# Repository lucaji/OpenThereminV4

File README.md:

# OpenTheremin v4.x platformio IDE

a new fork for the open source Theremin instrument software and hardware project by [GaudiLabs](https://github.com/GaudiLabs/OpenThereminV4). Adapted for [platformio](https://platformio.org/) IDE. Schematics, printed circuit board (PCB) design, bill of materials (BOM) and Arduino UNO compatible software for the OpenTheremin v4.x

> This repository brings an refactored, cleaned, fully commented and slightly optimized firmware for all OpenTheremin v4.x boards.

Lots of experimentation with this firmware is possible, check `build.h` for options.

## Waveform interpolation

Three waveform interpolation algorithms are included for experimenting with the 328p DDS generation:

- NONE (LEGACY)
- LINEAR
- HERMITE
- CATMULL-ROM (pushing the limits of the 328p - computational hungry!)

There is an interactive mode where each mode can be selected by muting/unmuting the Theremin. Using the NONE (LEGACY) mode, gives anyway a clean spectrum content on the audio output, fast responsiveness and an extended pitch range because of the optimizations that were already in place in the original OpenTheremin firmware.

## Serial port configuration

- Off (saves resources!)
- DEBUG (gives some state information)
- MIDI (emits MIDI data at 31250bps)

## Open Source Theremin based on the Arduino Platform

OpenTheremin is an arduino based real Theremin instrument. The legendary music instrument was invented by [Leon Theremin](https://www.google.com/url?sa=t&source=web&rct=j&opi=89978449&url=https://it.wikipedia.org/wiki/Lev_Sergeevi%25C4%258D_Termen) back in 1920.

The Theremin is played with both hands around two antennas, one to control the pitch and the other for volume expressivity.

The fully assembled version 4.x of OpenTheremin leverages two heterodyne VCO oscillators (voltage controlled) to measure the distance of the hands to each antenna while playing the instrument, by comparing those frequencies with two fixed frequency local oscillators.

The resulting signals (beating) are fed to and processed by a AtMega328P microcontroller which applies linearization and filtering in real-time, generating the sound reflecting the player's hands movements in the thin air.

There is an fast audio DAC onboard which delivers high quality digital audio, generated via a DDS (Direct Digital Synthesis) synth accessing serveral user-presettable and customizable wavetables to achieve different timbres.

## Instructions

This repo favours [VSCode + Platformio IDE](https://platformio.org/install/ide?install=vscode) as development environment instead of the Arduino IDE, still retaining compatibility though.

To fully enjoy a better development experience, it is advised to install Visual Studio Code and add the platformio IDE plug-in. After the latter has been installed, just opening the folder in VS Code will activate the platformio IDE.

## Ordering preassembled and tested boards

For more info on the open source project and on availability of ready made shield see:

https://www.gaudi.ch/OpenTheremin/

## Limits

> please be aware that the included DDS sound generator algorithm on a 16MHz 328p (Arduino UNO compatible) which is hardware driven by a two etherodyne RF VCO (voltage controlled oscillators) is already pushing the limits of the internal timers and interrupt pressure.

The lesser additional options you include in the build, the better sound quality:

- keep the serial port disabled if you don't need it.
- disable the CV/GATE outputs if you don't need them.
- select the desired interpolation mode if you like one - OFF otherwise!

#### LAST REVISION:

July 2025 by Luca Cipressi (lucaji.github.io)

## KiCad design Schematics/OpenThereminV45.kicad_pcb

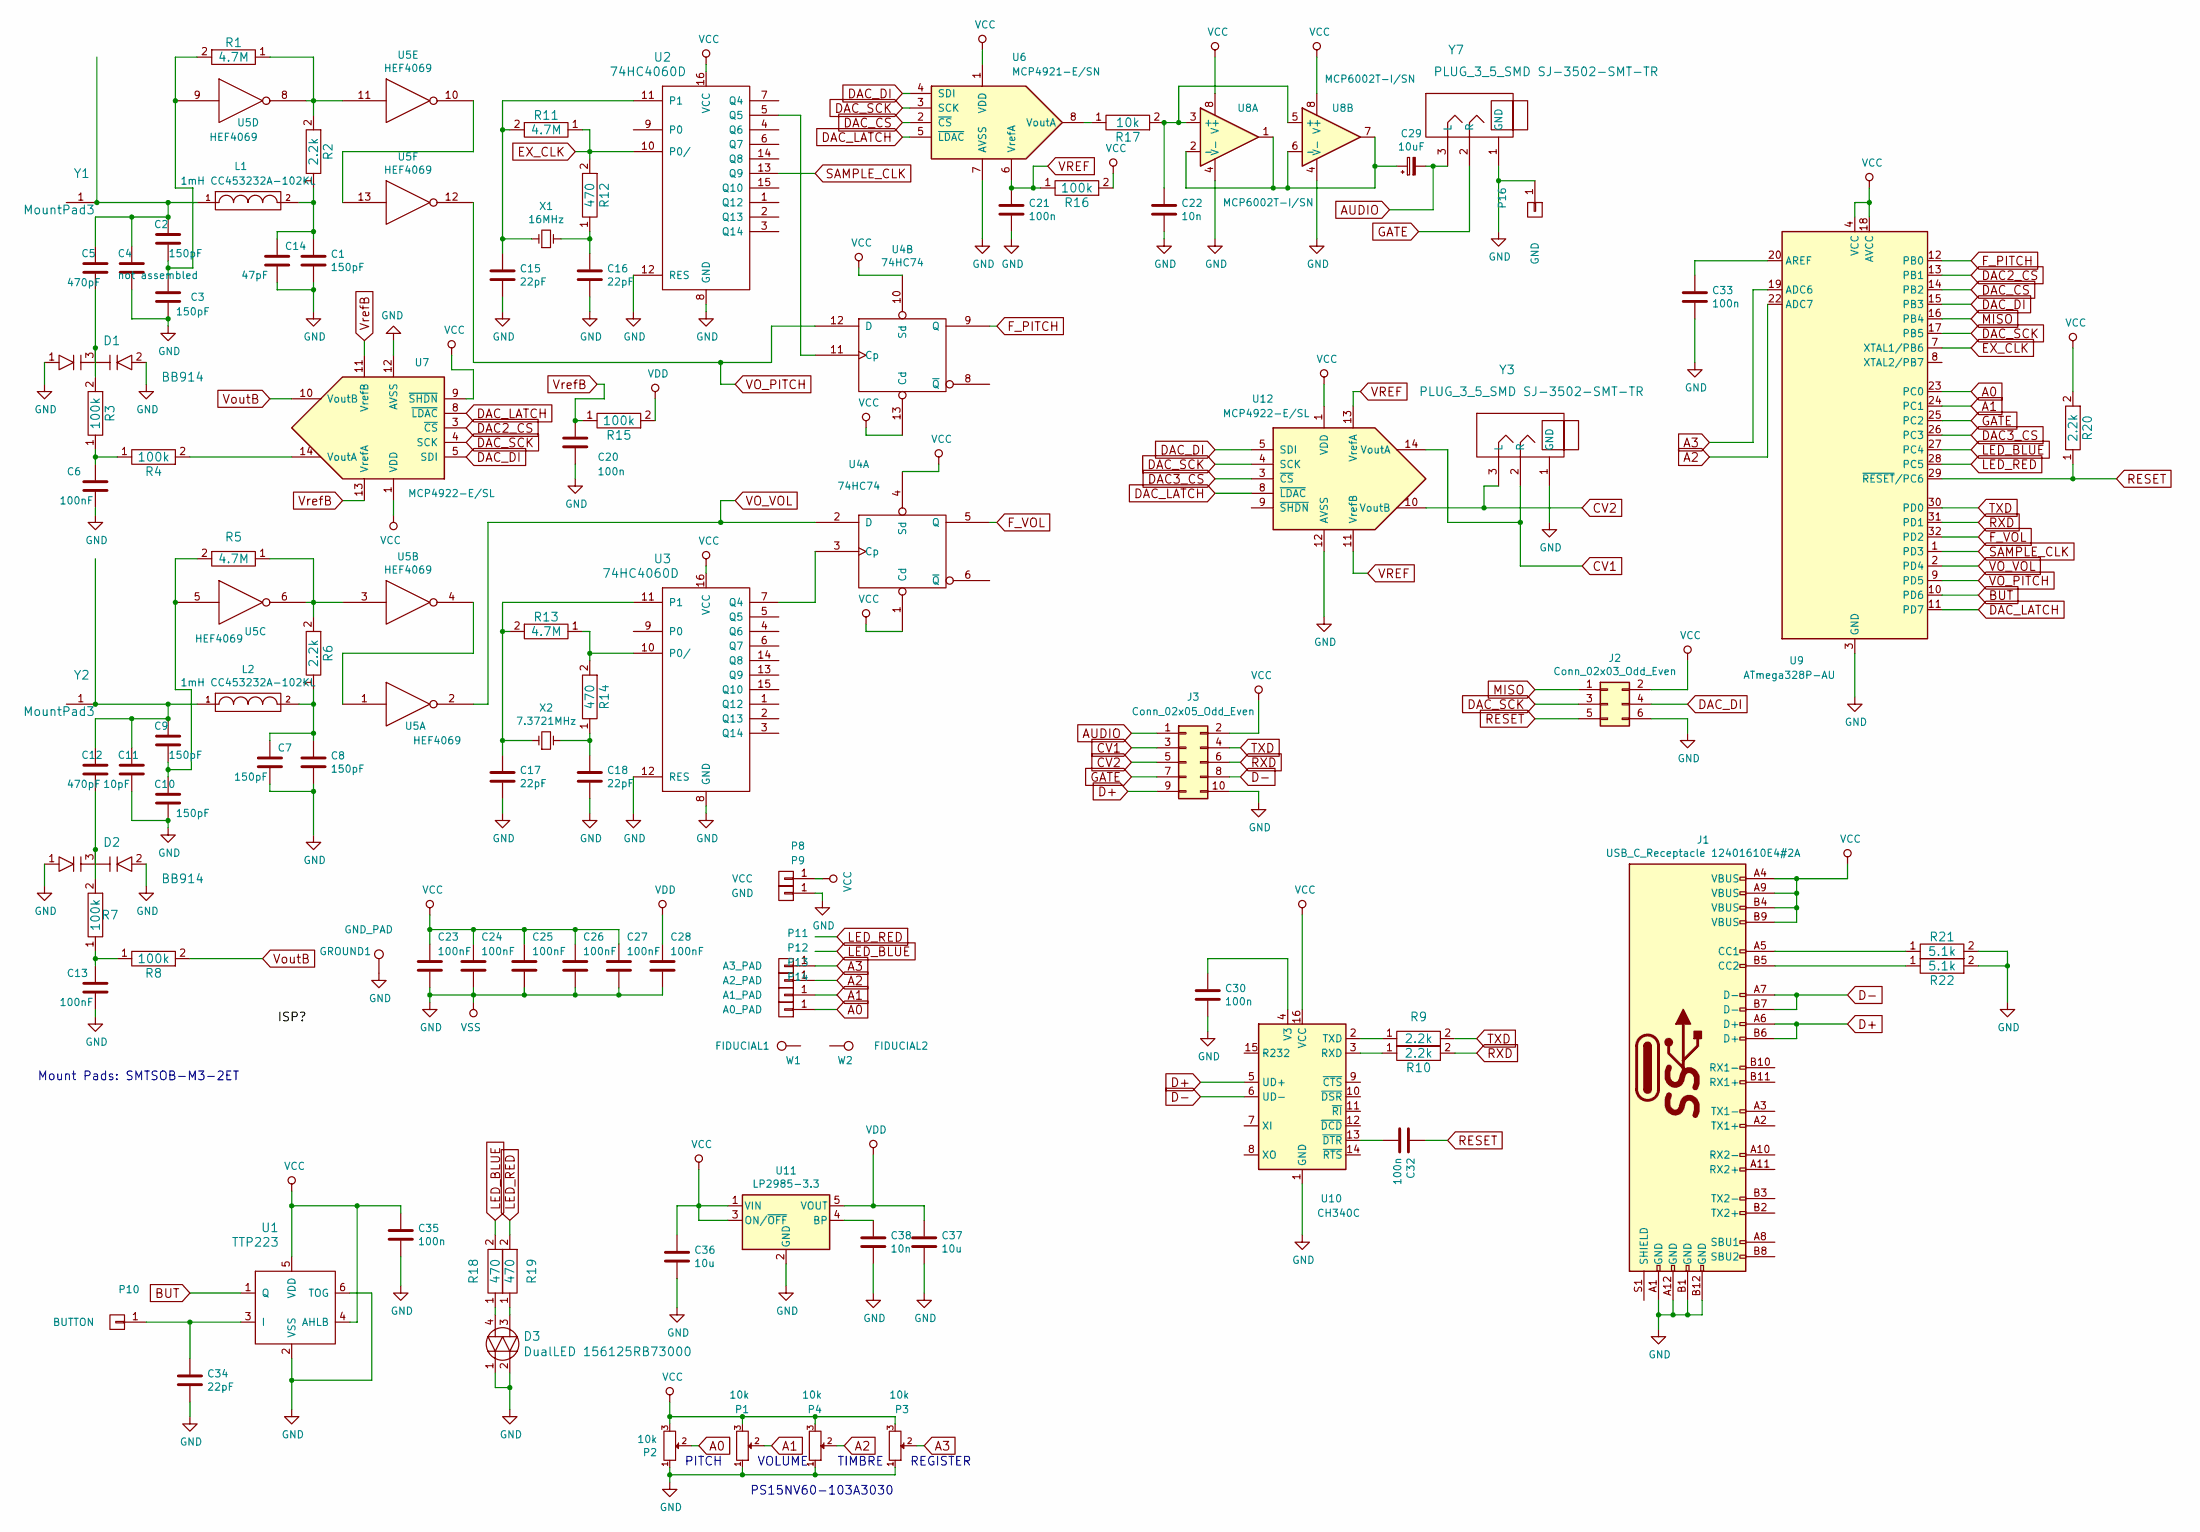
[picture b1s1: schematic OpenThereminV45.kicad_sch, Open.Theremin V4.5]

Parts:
C1, C2, C3, C7, C8, C9, C10: 150pF; C_0603_1608Metric
C4: not assembled; C_0603_1608Metric
C5, C12: 470pF; C_0603_1608Metric
C6, C13, C23, C24, C25, C26, C27, C28: 100nF; C_0603_1608Metric
C11: 10pF; C_0603_1608Metric
C14: 47pF; C_0603_1608Metric
C15, C16, C17, C18, C34: 22pF; C_0603_1608Metric
C20, C21, C30, C32, C33, C35: 100n; C_0603_1608Metric
C22, C38: 10n; C_0603_1608Metric
C29: 10uF; C_0603_1608Metric
C36, C37: 10u; C_0603_1608Metric
D1, D2: BB914; SOT-23
D3: DualLED 156125RB73000; WL-SBRW
GROUND1: GND_PAD; GNDPad
J1: USB_C_Receptacle 12401610E4#2A; USB_C_Receptacle_Amphenol_12401610E4-2A
J2: Conn_02x03_Odd_Even; Tag-Connect_TC2030-IDC-NL_2x03_P1.27mm_Vertical
J3: Conn_02x05_Odd_Even; PinHeader_2x05_P1.27mm_Vertical_SMD
L1, L2: 1mH CC453232A-102KL; COIL_T
P1, P2, P3, P4: 10k; PS15NV60
P8: VCC; SMD_Pinheader_1_OT_BLANK
P9, P16: GND; SMD_Pinheader_1_OT_BLANK
P10: BUTTON; SensorButton
P11: A3_PAD; SMD_Pinheader_1_OT_BLANK
P12: A2_PAD; SMD_Pinheader_1_OT_BLANK
P13: A1_PAD; SMD_Pinheader_1_OT_BLANK
P14: A0_PAD; SMD_Pinheader_1_OT_BLANK
R1, R5, R11, R13: 4.7M; R_0603_1608Metric
R2, R6, R9, R10, R20: 2.2k; R_0603_1608Metric
R3, R4, R7, R8, R15, R16: 100k; R_0603_1608Metric
R12, R14, R18, R19: 470; R_0603_1608Metric
R17: 10k; R_0603_1608Metric
R21, R22: 5.1k; R_0603_1608Metric
U1: TTP223; SOT-23-6
U2, U3: 74HC4060D; SOIC-16_3.9x9.9mm_P1.27mm
U4: 74HC74; SOIC-14_3.9x8.7mm_P1.27mm
U5: HEF4069; SOIC-14_3.9x8.7mm_P1.27mm
U6: MCP4921-E/SN; SOIC-8_3.9x4.9mm_P1.27mm
U7, U12: MCP4922-E/SL; SOIC-14_3.9x8.7mm_P1.27mm
U8: MCP6002T-I/SN; SOIC-8_3.9x4.9mm_P1.27mm
U9: ATmega328P-AU; TQFP-32_7x7mm_P0.8mm
U10: CH340C; SOIC-16_3.9x9.9mm_P1.27mm
U11: LP2985-3.3; SOT-23-5
W1: FIDUCIAL1; Fiducial_1mm_Dia_2.54mm_Outer_CopperBottom
W2: FIDUCIAL2; Fiducial_1mm_Dia_2.54mm_Outer_CopperBottom
X1: 16MHz; Crystal_SMD_HC49-SD
X2: 7.3721MHz; Crystal_SMD_HC49-SD
Y1, Y2: MountPad3; SMTSOB_M3
Y3, Y7: PLUG_3_5_SMD SJ-3502-SMT-TR; SJ-3502-SMT-TR

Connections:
A0: P2.2, P14.1, U9.23 (PC0)
A1: P1.2, P13.1, U9.24 (PC1)
A2: P4.2, P12.1, U9.22 (ADC7)
A3: P3.2, P11.1, U9.19 (ADC6)
AUDIO: C29.2, J3.1, Y7.3 (L)
BUT: U1.1 (Q), U9.10 (PD6)
CV1: J3.3, U12.14 (VoutA), Y3.2 (R)
CV2: J3.5, U12.10 (VoutB), Y3.3 (L)
D+: J1.A6 (D+), J1.B6 (D+), J3.9, U10.5 (UD+)
D-: J1.A7 (D-), J1.B7 (D-), J3.8, U10.6 (UD-)
DAC2_CS: U7.3 (~CS), U9.13 (PB1)
DAC3_CS: U9.26 (PC3), U12.3 (~CS)
DAC_CS: U6.2 (~CS), U9.14 (PB2)
DAC_DI: J2.4, U6.4 (SDI), U7.5 (SDI), U9.15 (PB3), U12.5 (SDI)
DAC_LATCH: U6.5 (~LDAC), U7.8 (~LDAC), U9.11 (PD7), U12.8 (~LDAC)
DAC_SCK: J2.3, U6.3 (SCK), U7.4 (SCK), U9.17 (PB5), U12.4 (SCK)
EX_CLK: R11.1, R12.2, U2.10 (P0/), U9.7 (XTAL1/PB6)
F_PITCH: U4.9 (Q), U9.12 (PB0)
F_VOL: U4.5 (Q), U9.32 (PD2)
GATE: J3.7, U9.25 (PC2), Y7.2 (R)
GND: C1.2, C3.2, C4.2, C6.2, C7.2, C8.2, C10.2, C11.2, C13.2, C14.2, C15.2, C16.2, C17.2, C18.2, C20.2, C21.2, C22.2, C23.2, C24.2, C25.2, C26.2, C27.2, C28.2, C30.2, C33.2, C34.2, C35.2, C36.2, C37.2, C38.2, D1.1, D1.2, D2.1, D2.2, D3.1, D3.2, GROUND1.1, J1.A1 (GND), J1.A12 (GND), J1.B1 (GND), J1.B12 (GND), J2.6, J3.10, P1.1, P2.1, P3.1, P4.1, P9.1, P16.1, R21.2, R22.2, U1.2 (VSS), U1.6 (TOG), U2.8 (GND), U2.12 (RES), U3.8 (GND), U3.12 (RES), U4.7 (GND), U5.7 (VSS), U6.7 (AVSS), U7.12 (AVSS), U8.4 (V-), U9.3 (GND), U9.5 (GND), U9.21 (GND), U10.1 (GND), U11.2 (GND), U12.12 (AVSS), Y3.1 (GND), Y7.1 (GND)
LED_BLUE: R18.2, U9.27 (PC4)
LED_RED: R19.2, U9.28 (PC5)
MISO: J2.1, U9.16 (PB4)
unnamed: C1.1, C14.1, L1.2, R2.1
unnamed: C2.1, C4.1, C5.1, L1.1, Y1.1
unnamed: C5.2, D1.3, R3.2
unnamed: C6.1, R3.1, R4.1
unnamed: C7.1, C8.1, L2.2, R6.1
unnamed: C9.2, C10.1, R5.2, U5.5
unnamed: C9.1, C11.1, C12.1, L2.1, Y2.1
unnamed: C12.2, D2.3, R7.2
unnamed: C13.1, R7.1, R8.1
unnamed: C15.1, R11.2, U2.11 (P1), X1.1
unnamed: C16.1, R12.1, X1.2
unnamed: C17.1, R13.2, U3.11 (P1), X2.1
unnamed: C18.1, R14.1, X2.2
unnamed: C22.1, R17.2, U8.3 (+), U8.5 (+)
unnamed: C29.1, U8.1, U8.2 (-), U8.6 (-), U8.7
unnamed: C30.1, U10.4 (V3)
unnamed: C32.2, U10.13 (~DTR)
unnamed: C33.1, U9.20 (AREF)
unnamed: C34.1, P10.1, U1.3 (I)
unnamed: C38.1, U11.4 (BP)
unnamed: D3.3, R19.1
unnamed: D3.4, R18.1
unnamed: J1.A5 (CC1), R21.1
unnamed: J1.B5 (CC2), R22.1
unnamed: R1.1, R2.2, U5.8, U5.11
unnamed: C2.2, C3.1, R1.2, U5.9
unnamed: R4.2, U7.14 (VoutA)
unnamed: R5.1, R6.2, U5.3, U5.6
unnamed: R9.1, U10.2 (TXD)
unnamed: R10.1, U10.3 (RXD)
unnamed: R13.1, R14.2, U3.10 (P0/)
unnamed: R17.1, U6.8 (VoutA)
unnamed: U2.5 (Q5), U4.11 (Cp)
unnamed: U3.7 (Q4), U4.3 (Cp)
unnamed: U5.1, U5.4
unnamed: U5.10, U5.13
RESET: C32.1, J2.5, R20.1, U9.29 (~RESET/PC6)
RXD: J3.6, R10.2, U9.31 (PD1)
SAMPLE_CLK: U2.13 (Q9), U9.1 (PD3)
TXD: J3.4, R9.2, U9.30 (PD0)
VCC: C23.1, C24.1, C25.1, C26.1, C27.1, C35.1, C36.1, J1.A4 (VBUS), J1.A9 (VBUS), J1.B4 (VBUS), J1.B9 (VBUS), J2.2, J3.2, P1.3, P2.3, P3.3, P4.3, P8.1, R16.2, R20.2, U1.4 (AHLB), U1.5 (VDD), U2.16 (VCC), U3.16 (VCC), U4.1 (Cd), U4.4 (Sd), U4.10 (Sd), U4.13 (Cd), U4.14 (VCC), U6.1 (VDD), U7.1 (VDD), U7.9 (~SHDN), U8.8 (V+), U9.4 (VCC), U9.6 (VCC), U9.18 (AVCC), U10.16 (VCC), U11.1 (VIN), U11.3 (ON/~OFF), U12.1 (VDD)
VDD: C28.1, C37.1, R15.2, U5.14 (VDD), U11.5 (VOUT)
VO_PITCH: U4.12 (D), U5.12, U9.9 (PD5)
VO_VOL: U4.2 (D), U5.2, U9.2 (PD4)
VREF: C21.1, R16.1, U6.6 (VrefA), U12.11 (VrefB), U12.13 (VrefA)
VoutB: R8.2, U7.10 (VoutB)
VrefB: C20.1, R15.1, U7.11 (VrefB), U7.13 (VrefA)

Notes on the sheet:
REGISTER
VOLUME
TIMBRE
PITCH
PS15NV60-103A3030
Mount Pads: SMTSOB-M3-2ET

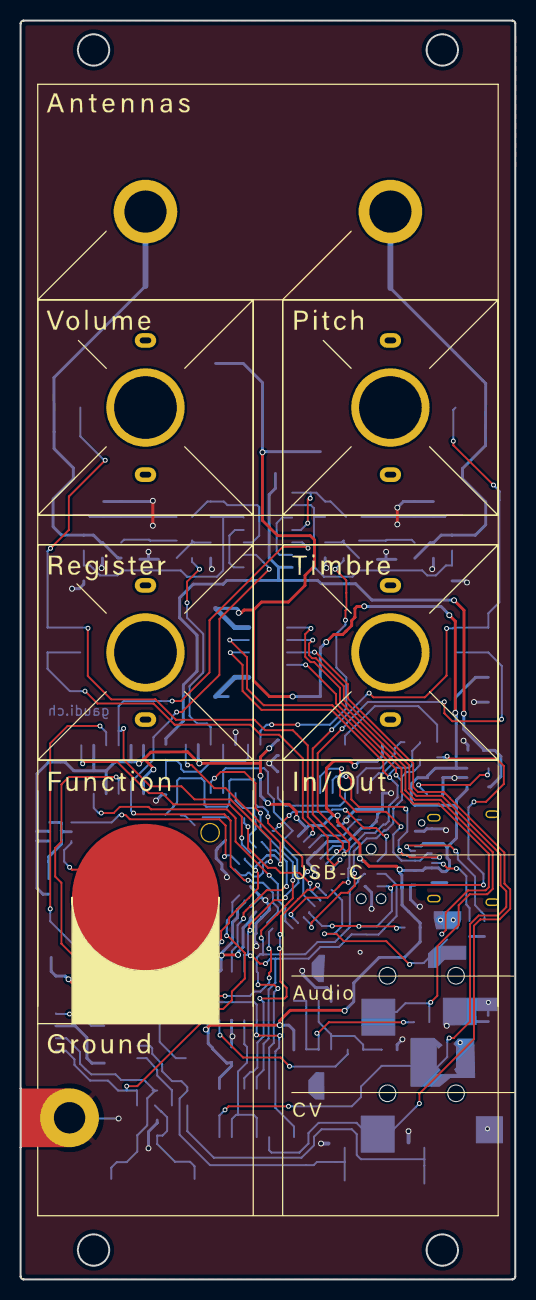
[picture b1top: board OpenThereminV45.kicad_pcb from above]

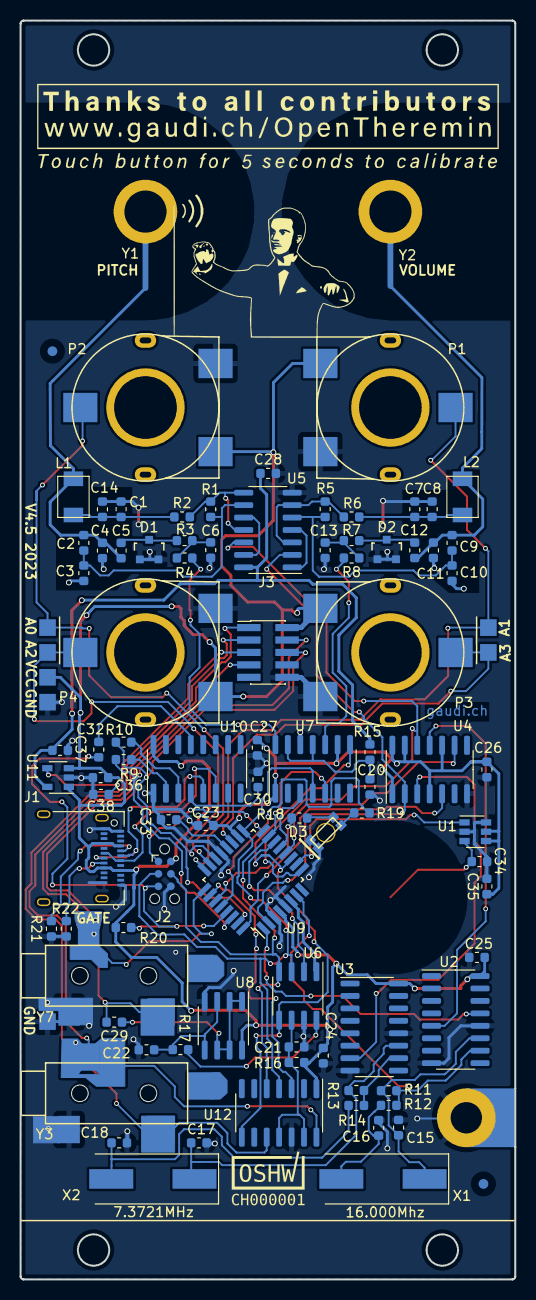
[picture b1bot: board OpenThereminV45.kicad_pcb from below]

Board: 2 copper layers, 50.5 x 128.5 mm, 99 parts (95 on the bottom side), 71 nets.

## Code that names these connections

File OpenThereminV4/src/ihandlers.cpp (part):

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
static const uint32_t MCP_DAC_BASE = 2048;

#define F_VOL_PIN (PIND & (1 << PORTD2))
#define F_PITCH_PIN (PINB & (1 << PORTB0))

volatile uint16_t vScaledVolume = 0;        // output level amplitude
volatile uint16_t vPointerIncrement = 0;    // phase accumulator increment
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 *
 * This function sets up:
 * - Timer1 in normal mode with input capture on rising edge at full 16 MHz clock rate,
 *     used to measure the frequency of the pitch oscillator via the ICP1 pin (PD5 / Digital 5).
 * - Timer0 with Arduino default Fast PWM mode and a 64× prescaler,
 *     which supports core timing functions like `millis()` and `delay()`.
 *
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 *
 * @note
 * - Timer1 is configured to run without prescaling for maximum frequency resolution.
 * - The ICES1 bit ensures rising edge detection on ICP1 (PD5).
 * - No waveform output is enabled; timers are used strictly for counting.
 */
void ihInitialiseTimer() {
    // --- Timer1: Pitch frequency measurement (ICP1 on PD5) ---        
    /**
     * TCCR1A controls waveform generation mode and output compare behavior.
     * Setting it to 0 disables waveform output on OC1A/OC1B and enables normal counting mode.
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 *
 * This function sets up the External Interrupt Control Register (EICRA) to trigger interrupts
 * on rising edges for both INT0 (volume gate, F_VOL) and INT1 (sample clock / wave generator tick).
 * These are connected respectively to PD2 (INT0) and PD3 (INT1) on the ATmega328P.
 *
 * - INT0 is used to latch volume oscillator timing information from the flip-flop gate.
 * - INT1 triggers the main waveform ISR for audio output and pitch/volume tracking.
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 *             would be implemented with attachInterrupt() or direct NVIC/GPIO interrupt configuration.
 */
void ihInitialiseInterrupts() {
    // --- Configure interrupt trigger type for INT0 (PD2) and INT1 (PD3) ---

    /* EICRA – External Interrupt Control Register A
            ISC00 + ISC01 = 1 + 1 = Rising edge trigger for INT0 (Volume)
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 * using the full 16 MHz system clock, with overflow interrupt enabled.
 * It’s typically called during absolute pitch calibration or special diagnostic modes.
 *
 * The RF oscillator signal (VO_PITCH) enters on PD5 (ICP1 / T1), and its rising edge
 * transitions are captured by periodically reading the counter value (TCNT1).
 *
 * Configuration:
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 * - CV output if enabled.
 *
 * ## Signal Input Explanation
 * - `F_PITCH_STATE` reads pin PB0 (digital pin 8) — the F_PITCH signal after flip-flop.
 *     Defined as: `(PINB & (1 << PORTB0))` → true when PB0 is HIGH.
 *
 * - `F_VOL_STATE` reads pin PD2 (digital pin 2) — the F_VOL signal after flip-flop.
 *     Defined as: `(PIND & (1 << PORTD2))` → true when PD2 is HIGH.
 *
 * These signals are fed from the logic divider+flip-flop gates for pitch and volume.
 * A rising edge indicates a new gated RF cycle suitable for timing measurement.
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 * - debounce method: 3-sample debounce followed by 2-sample confirmation.
 *
 * Externaly generated 31250 Hz Interrupt for WAVE generator (32us) 
 * 16MHz / 512 (2^9) = 31250 SAMPLE_CLK PD3
 * 
 * @note Keep interrupt duration below sample period (~32 µs).
 */
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        static bool lastPC = false;     ///< last pitch counter
        static bool lastVC = false;     ///< last volume counter

        bool currentPC = F_PITCH_PIN;   ///< Read F_PITCH signal on PB0 (digital pin 8)
        bool currentVC = F_VOL_PIN;     ///< Read F_VOL signal on PD2 (digital pin 2)

        // --- F_PITCH Rising Edge Detection (PB0)
        if (currentPC && !lastPC) {
            pitch_counter = ICR1;                            ///< Capture current Timer1 count
            pitch = pitch_counter - pitch_counter_l;         ///< Compute elapsed ticks
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        }
        lastPC = currentPC;

        // --- F_VOL Rising Edge Detection (PD2)
        if (currentVC && !lastVC) {
            vol_counter = vol_counter_i;                     ///< Volume measured indirectly via TCNT1
            vol = vol_counter - vol_counter_l;
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        lastVC = currentVC;
    #else
        // legacy debounce
        // PB0 == F_PITCH
        if (F_PITCH_PIN) { debounce_p++; }
        if (debounce_p == 3) {
            noInterrupts();
            pitch_counter = ICR1;                               ///< Get Timer-Counter 1 value
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            pitch_counter_l = pitch_counter;                    ///< Set actual value as new last value
        } else if (debounce_p == 5) { pitchValueAvailable = true; }

        // PD2 == F_VOL
        if (F_VOL_PIN) { debounce_v++; }
        if (debounce_v == 3) {
            noInterrupts();
            vol_counter = vol_counter_i;                        ///< Get Timer-Counter 1 value
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
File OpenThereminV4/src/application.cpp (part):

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#define HW_BUTTON_PRESSED       (HW_BUTTON_STATE == LOW)
#define HW_BUTTON_RELEASED      (HW_BUTTON_STATE != LOW)

#define LED_BLUE_PIN 18
#define HW_LED_BLUE_ON          (PORTC |= (1<<PORTC4))
#define HW_LED_BLUE_OFF         (PORTC &= ~(1<<PORTC4))
#define HW_LED_BLUE_TOGGLE      (PORTC = PORTC ^ (1<<PORTC4))

#define LED_RED_PIN 19
#define HW_LED_RED_ON           (PORTC |= (1<<PORTC5))
#define HW_LED_RED_OFF          (PORTC &= ~(1<<PORTC5))
#define HW_LED_RED_TOGGLE       (PORTC = PORTC ^ (1<<PORTC5))
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        #endif

    pinMode(BUTTON_PIN, INPUT_PULLUP);
    pinMode(LED_BLUE_PIN, OUTPUT);
    pinMode(LED_RED_PIN, OUTPUT);

    HW_LED_RED_ON; HW_LED_BLUE_OFF; // standby mode

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
            if (!gate_p && (tmpVolume >= GATE_ON)) {
                gate_p = true;
                // pull the gate up to sense, first (to prevent short-circuiting the IO pin:
                GATE_PULLUP;
                if (GATE_SENSE) { 
                    // if it goes up, drive the gate high
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 * @brief Measures the frequency of the SAMPLE_CLK signal (from Q9 of 74HC4060).
 *
 * This function uses Timer1 on the ATmega328P to measure how many clock ticks (at 16 MHz)
 * occur during 31,250 rising edges of the SAMPLE_CLK signal on digital pin 3 (PD3).
 * This corresponds to one full second if SAMPLE_CLK is exactly 31.25 kHz,
 * as expected when Q9 = 16 MHz / 512.
 * 
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 * - Timer1 counter (TCNT1) and overflow counter are combined to form a 32-bit tick count.
 * - This function is blocking and should not be used in real-time critical paths.
 *
 * @note Digital pin 3 (PD3) must be connected to the SAMPLE_CLK signal.
 * @return Total tick count at 16 MHz after 31,250 rising edges — used to compute real frequency.
 */
unsigned long Application::GetQMeasurement() {
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 *
 * This function uses Timer1 in normal mode to count the number of clock cycles
 * over a 1-second window (via `delay(1000)`) to compute the frequency of the
 * signal arriving on PD5 (ICP1).
 *
 * Timer1 is configured with a prescaler of 1024, so its effective counting frequency is:
 *   16,000,000 / 1024 = 15,625 Hz.
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 * @brief Measures the frequency of the volume antenna oscillator (VO_VOL).
 *
 * This function uses Timer/Counter0 in external clock mode to count rising edges
 * from the VO_VOL signal (connected to T0 / PD4 / Digital Pin 4) over a 1-second
 * gate window determined by Timer1 overflow.
 *
 * Timer1 is preloaded with 49911 to overflow after ~1 second (65536 - 49911 = 15625 ticks @ 16 MHz).
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    timer_overflow_counter = 0;                                 ///< Clear overflow tracker for Timer0
    TCNT0 = 0;                                                  ///< Reset Timer0 (pulse counter)
    TCNT1 = 49911;                                              ///< Preload Timer1 so it overflows in 1s (65536 - 49911 = 15625 ticks @ 16 MHz)
    // Set Timer0 to external clock on T0 (PD4), count on rising edge
    TCCR0B = (1 << CS02) | (1 << CS01) | (1 << CS00);
    // Clear Timer1 overflow flag (to detect overflow event)
    TIFR1 = (1 << TOV1);                                        //Timer1 INT Flag Reg: Clear Timer Overflow Flag
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
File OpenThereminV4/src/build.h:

/**
 * @file build.h
 * @brief Build options for OpenTheremin
 *
 * Define directives for custom build options
 *
 * REVISION HISTORY
 * July 2025 Luca Cipressi (lucaji.github.io) added extended serial modes and interpolation.
 * (c) GNU GPL v3 or later.
 */

#ifndef _BUILD_H_
#define _BUILD_H_

// SERIAL_MODE sets the USB Serial speed according selected functionality
// for better audio output quality, set it off as it saves precious resources.
// the MIDI mode DOES NOT enable the OpenTheremin as a MIDI compliant USB device
// you will need a software on your PC to convert USB serial MIDI data into a virtual MIDI port.
#define SERIAL_MODE_OFF 0               // disables the use of the serial port entirely
#define SERIAL_MODE_DEBUG 1             // initializes the serial port at 57600 bps and emits debug information
#define SERIAL_MODE_MIDI 2              // Initializes the serial port at 31250 bps and emits MIDI note (experimental)
// select one option from above
#define SERIAL_MODE SERIAL_MODE_OFF

#if SERIAL_MODE == SERIAL_MODE_DEBUG
  #define DEBUG_PRINT(x)     Serial.print(x)
  #define DEBUG_PRINTLN(x)   Serial.println(x)
#else
  #define DEBUG_PRINT(x)     ((void)0)
  #define DEBUG_PRINTLN(x)   ((void)0)
#endif

/*
 * AUDIO FEEDBACK
 * 
 * 
 */
// if defined, will emit sound feedback
// comment it out for silent operation (only LED feedback)
//#define ENABLE_AUDIO_FEEDBACK

/*
 * CV_OUTPUT_MODE sets options for the CV output jack
 *
 * for better audio output quality, set it off as it saves precious resources
 * especially if you don't need CV/GATE outputs. Refer to each option's comment
 * for description.
 * 
 * 
 */
#define CV_OUTPUT_MODE_OFF 0            // disables the CV output - this saves resources - for a slightly better audio quality if not needed at all.
#define CV_OUTPUT_MODE_LOG 1            // uses a logarithmic curve for CV output (1V/Oct for Moog & Roland)
#define CV_OUTPUT_MODE_LINEAR 2         // uses a linear transfer function for CV output (819Hz/V for Korg & Yamaha)
#define CV_OUTPUT_MODE CV_OUTPUT_MODE_OFF

/*
 * GATE OUTPUT
 *
 */
// Set the trigger levels for the Gate signal (0 to 127 in preparation for later MIDI extensions)
#define GATE_ON  20 // That's the level which will drive the Gate high when volume increases from lower
#define GATE_OFF 16 // That's the level which will drive the Gate low when volume decreases from higher
// Making both values equal risk the gate signal to bounce, leave at least 4 (hysteresis) between both.
// Set both to 128 to disable the Gate Signal.

/*
 * SAMPLE INTERPOLATION (EXPERIMENTAL)
 * 
 * these switches will activate different smoothing algorithms trading off the
 * computational efficiency and the resulting harmonic content of the output wavetable
 * given the limitations of the wavetable size and the strict timing needed for the
 * DDS generator to complete the ISR routine especially on the 328p at 16MHz
 * 
 * - INTERPOLATION_NONE
 *   the best results are guaranteed with the original algorithm used in OpenTheremin
 *   because the table step matches a power-of-2 accumulator (phase alignment),
 *   No risk of overshooting, clipping, or interpolator curve "ripples",
 *   Less CPU jitter: less timing variability = more phase-coherent output.
 *   -> Optimal harmonic distortion (clean FFT)
 *   -> High responsiveness (fast reaction time)
 *   -> Higher frequency limit in pitch generation (4kHz)
 * 
 * - INTERPOLATION_LINEAR
 *   smooths the lower frequencies, but introduces some harmonic content
 * 
 * - INTERPOLATION_HERMITE - INTERPOLATION_CATMULL_ROM
 *   very high computation budget and introduces significant latency
 *   At 4 kHz pitch = 128 samples/ms = 32 µs per sample budget
 *   Catmull/Hermite easily consume 20–28 µs, leaving very little headroom.
 *   Lower max pitch:
 *   Due to ISR latency, sample generation can't keep up → dropped samples = lower actual frequency.
 *   Both introduce curvature that adds non-sinusoidal partials.
 * 
 * - INTERPOLATION_MODE_INTERACTIVE
 *   for testing and experimental purposes, it will advance each of the previous modes
 *   everytime the user switches between MUTE and UNMUTE (by touching once the touch button)
 *   make sure you activate the serial port for debug to see which mode is engaged.
 * 
 * [Hermite Interpolation](https://en.wikipedia.org/wiki/Hermite_interpolation)
 * [Catmull-Rom Spline](https://en.wikipedia.org/wiki/Cubic_Hermite_spline#Catmull%E2%80%93Rom_spline)
 * 
 */
#define INTERPOLATION_NONE        0             // best choice for 328p, clean harmonic content, highest responsiveness, higher pitch range
#define INTERPOLATION_LINEAR      1             // smooths low-frequency pitches, introduces slight harmonic content
#define INTERPOLATION_HERMITE     2             // heavy computing budget - introduces latency
#define INTERPOLATION_CATMULL_ROM 3             // heavy computing budget - introduces latency
#define INTERPOLATION_MODE_INTERACTIVE 127      // for testing purposes, includes all the above code, but at each mute->unmute operation it will rotate between the modes.
#define INTERPOLATION_MODE INTERPOLATION_NONE

/*
 * INCLUDES A PRECISE PURE SINEWAVE IF DEFINED
 * as waveform at index 0 (the very first)
 * 
 * useful for test purposes (FFT) or to be played as a very neutral timbre
 * 
 * this sinewave generates an almost pure harmonic content
 * it still will have limitations because of the limited (1024 points) table
 * and the strict timing implemented in this current OpenTheremin firmware.
 * 
 * none of standard wavetables included with OpenTheremin
 * are not perfect sinewaves, as the original Theremin timbre
 * has its own timbre. the OT wavetables mimic those original
 * sounding waveforms pretty accurately.
 * 
 */
//#define WAVEFORM_INCLUDE_PURE_SINE

/*
 * PITCH and VOLUME measurement debounce strategy
 * 
 * - LEGACY debounces over 5 pulses before flagging the reading as ready.
 * - EDGE_DETECT is faster and does not block interrupts.
 */
#define DDS_DEBOUNCE_MODE_LEGACY 0
#define DDS_DEBOUNCE_MODE_EDGE_DETECT 1
#define DDS_DEBOUNCE_MODE DDS_DEBOUNCE_MODE_EDGE_DETECT

#endif // _BUILD_H_

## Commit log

2025-07-28 cleaned, optimized, commented and expanded for experiments
2025-07-28 set bare-minimum defaults
2025-08-11 clean up first pass: dead code removal, code reformat and consistent indentation, renamed and reordered all wavetable files as header files for includes (according C standard) not as .c files
2025-08-11 moved all hw macros in place, added macro constants for EEPROM configuration addresses
2025-08-11 expanded the build.h file with comments and cleaner options, cleaned the CV/GATE handling in main application, added serial debug macros instead of Serial.print statements
2025-08-11 added solid potentiometer reading logic with hysteresis check to minimize DDS impact, position now is correctly read at power-on too
2025-08-12 new solid calibration algorithm (with success/fail indication) moved to separate translation unit. Removed Application class in favour of plain C methods (no need to instantiate more than one class -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
2025-08-12 optimized DAC (ihandlers.cpp) by removing unnecessary interrupt blocking/unblocking calls - ISR has already highest prio. DAC code has now forced inlining and proper SPIF register clearing, removed u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
2025-11-06 Removing Application class and adding theremin_setup and theremin_loop.
2025-12-08 fixed compile error, restored UI colors as per User Manual, restored getQMeasurement routine.
2025-12-08 correct audio active at poweron - UI colors OK
